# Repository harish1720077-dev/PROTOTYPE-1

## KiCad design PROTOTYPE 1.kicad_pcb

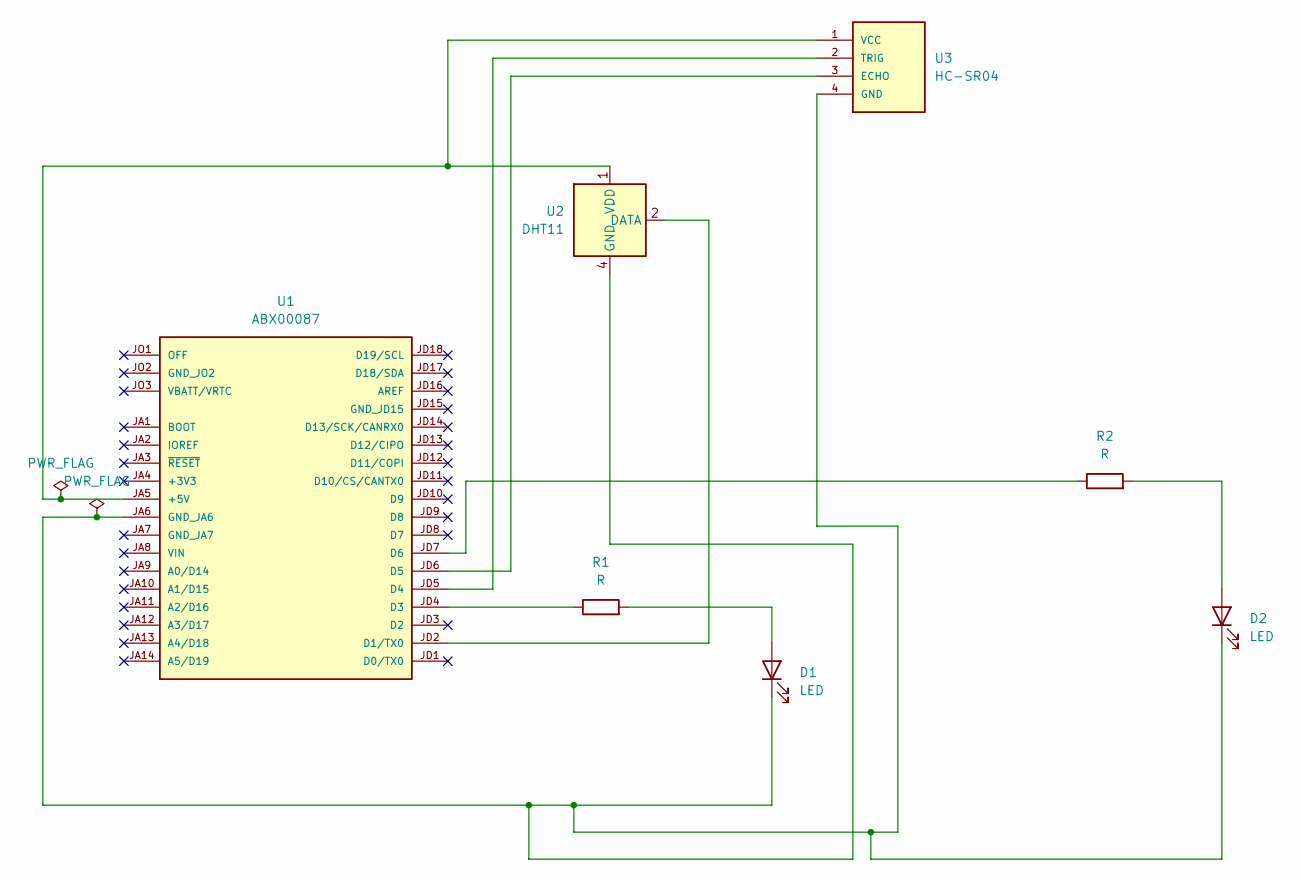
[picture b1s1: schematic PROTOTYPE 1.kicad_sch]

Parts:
D1, D2: LED; LED_D5.0mm
R1, R2: R; R_Axial_DIN0207_L6.3mm_D2.5mm_P7.62mm_Horizontal
U1: ABX00087; MODULE_ABX00087; PARTREV 4
U2: DHT11; Aosong_DHT11_5.5x12.0_P2.54mm
U3: HC-SR04; XCVR_HC-SR04

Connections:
unnamed: D1.2 (A), R1.2
unnamed: D1.1 (K), D2.1 (K), U1.JA6 (GND_JA6), U2.4 (GND), U3.4 (GND)
unnamed: D2.2 (A), R2.2
unnamed: U1.JA5 (+5V), U2.1 (VDD), U3.1 (VCC)
unnamed: U1.JD2 (D1/TX0), U2.2 (DATA)
unnamed: R1.1, U1.JD4 (D3)
unnamed: U1.JD5 (D4), U3.2 (TRIG)
unnamed: U1.JD6 (D5), U3.3 (ECHO)
unnamed: R2.1, U1.JD7 (D6)

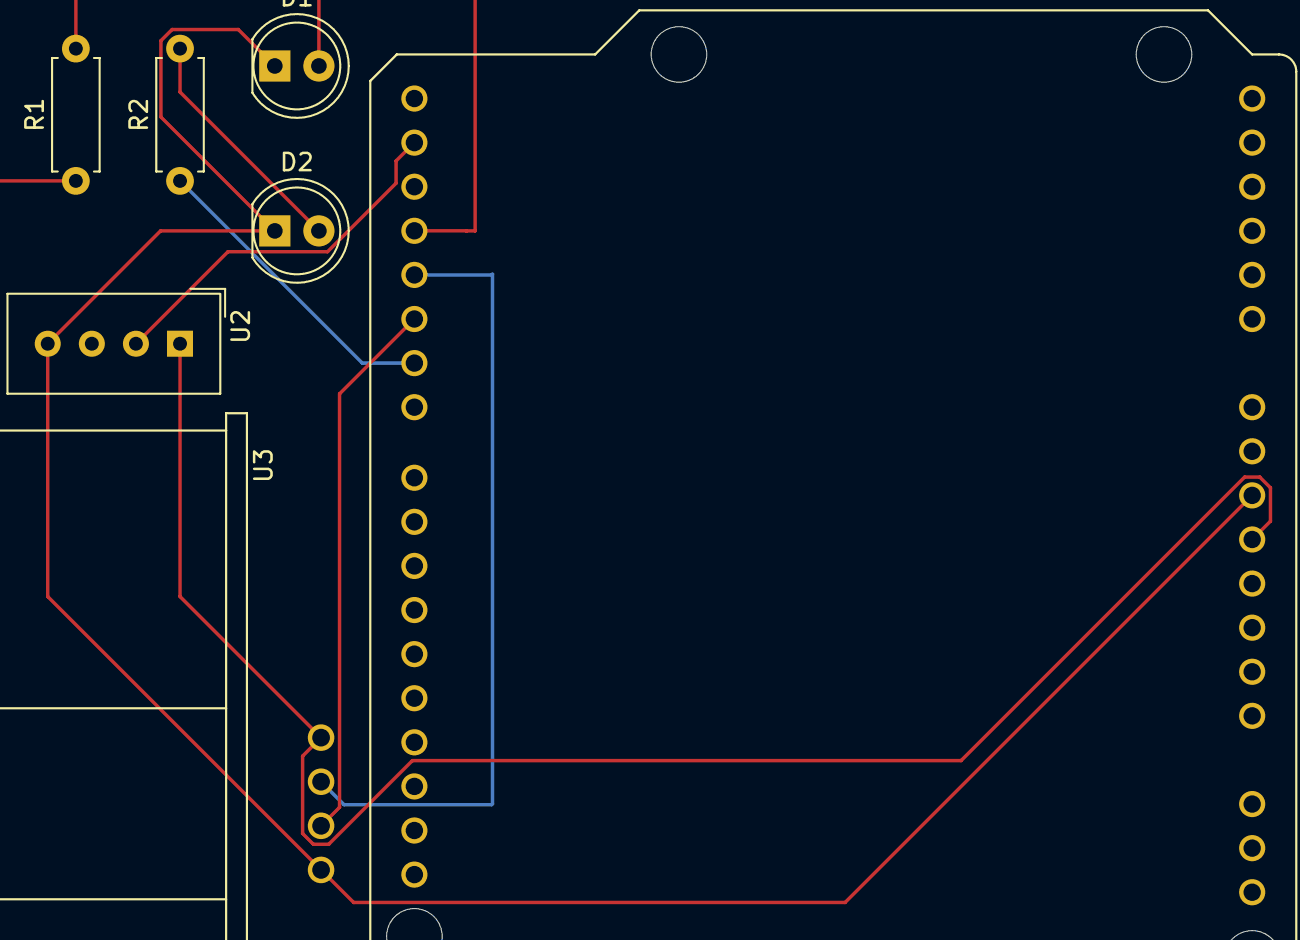
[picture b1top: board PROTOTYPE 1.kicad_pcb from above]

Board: 2 copper layers, 7 parts (0 on the bottom side), 9 nets.
